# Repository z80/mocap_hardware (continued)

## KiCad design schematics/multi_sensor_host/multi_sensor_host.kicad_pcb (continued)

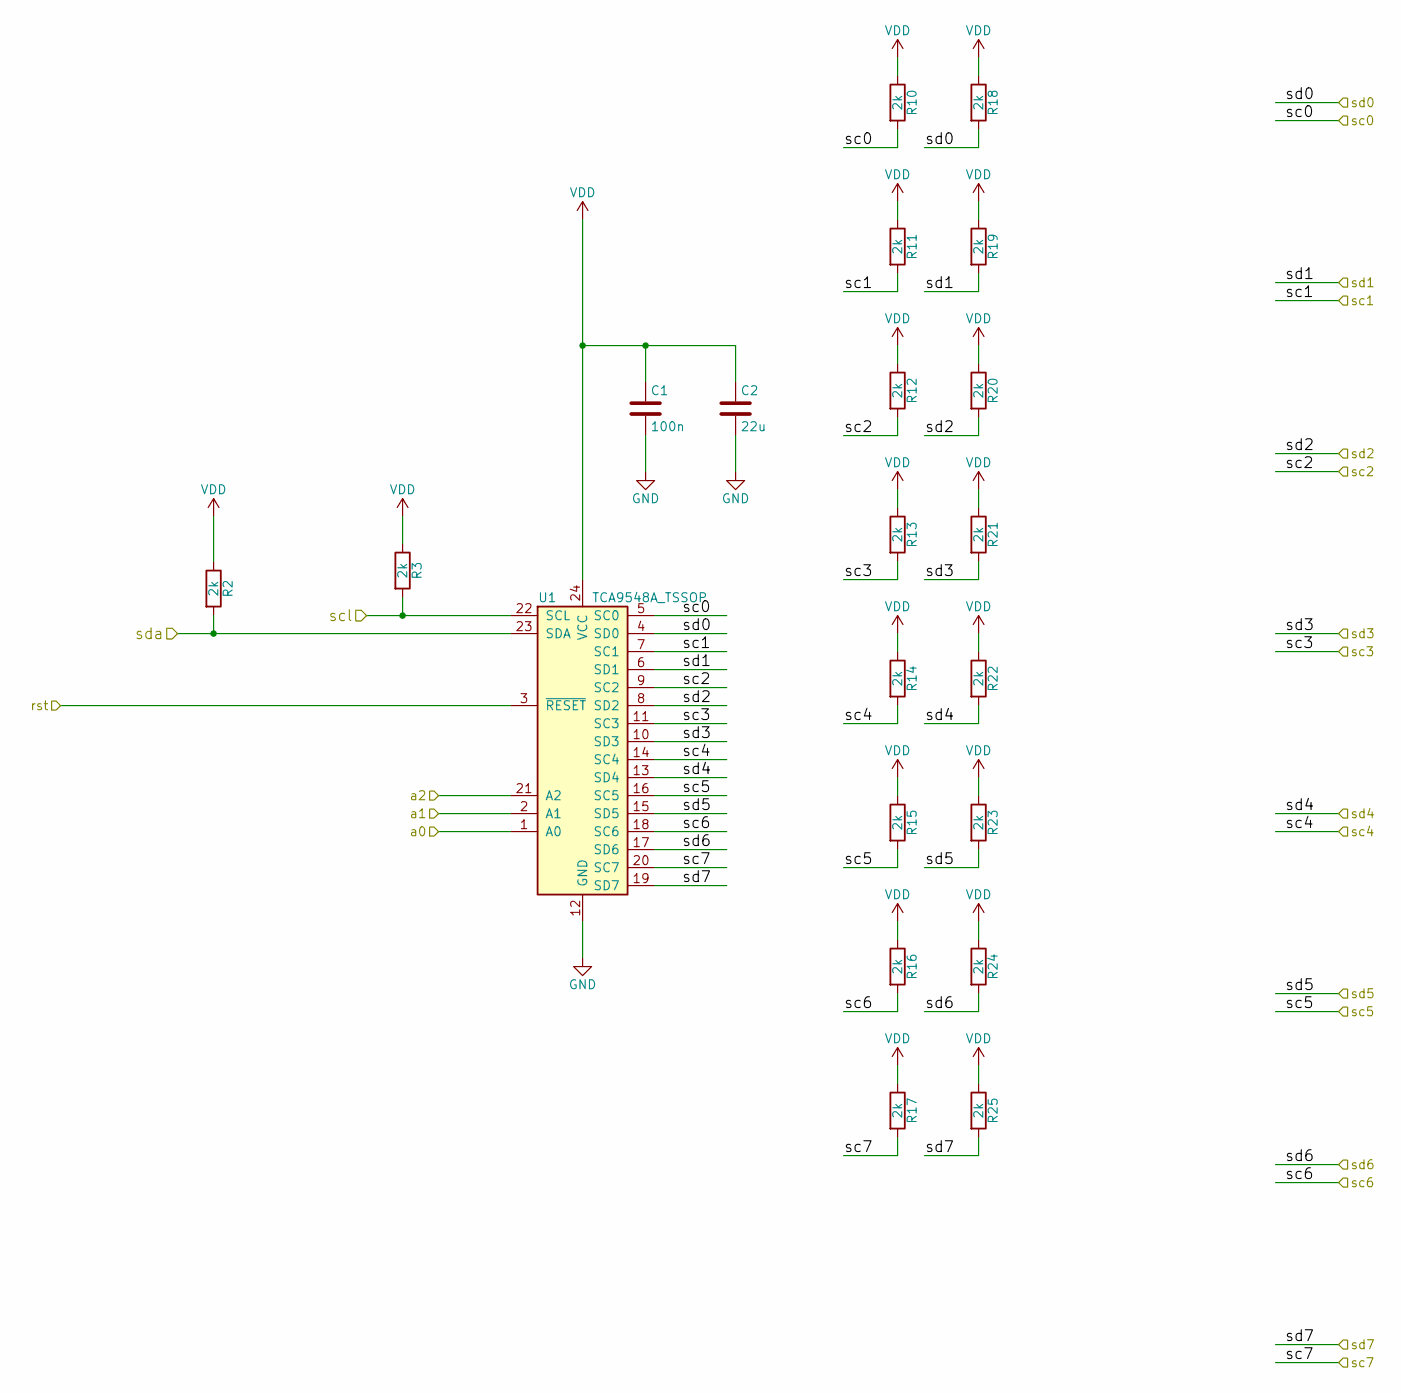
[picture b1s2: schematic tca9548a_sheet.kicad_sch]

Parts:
C1: 100n; C_0603_1608Metric
C2: 22u; C_0603_1608Metric
R2, R3, R10, R11, R12, R13, R14, R15, R16, R17, R18, R19, R20, R21, R22, R23, R24, R25: 2k; C_0603_1608Metric
U1: TCA9548A_TSSOP; TSSOP-24_4.4x7.8mm_P0.65mm

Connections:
/rst_mcu: U1.3 (~RESET); also elsewhere on the board
/scl_0: R10.2, U1.5 (SC0); also elsewhere on the board
/scl_1: R11.2, U1.7 (SC1); also elsewhere on the board
/scl_2: R12.2, U1.9 (SC2); also elsewhere on the board
/scl_3: R13.2, U1.11 (SC3); also elsewhere on the board
/scl_4: R14.2, U1.14 (SC4); also elsewhere on the board
/scl_5: R15.2, U1.16 (SC5); also elsewhere on the board
/scl_6: R16.2, U1.18 (SC6); also elsewhere on the board
/scl_7: R17.2, U1.20 (SC7); also elsewhere on the board
/scl_host_a: R3.2, U1.22 (SCL); also elsewhere on the board
/sda_0: R18.2, U1.4 (SD0); also elsewhere on the board
/sda_1: R19.2, U1.6 (SD1); also elsewhere on the board
/sda_2: R20.2, U1.8 (SD2); also elsewhere on the board
/sda_3: R21.2, U1.10 (SD3); also elsewhere on the board
/sda_4: R22.2, U1.13 (SD4); also elsewhere on the board
/sda_5: R23.2, U1.15 (SD5); also elsewhere on the board
/sda_6: R24.2, U1.17 (SD6); also elsewhere on the board
/sda_7: R25.2, U1.19 (SD7); also elsewhere on the board
/sda_host_a: R2.2, U1.23 (SDA); also elsewhere on the board
GND: C1.2, C2.2, U1.1 (A0), U1.2 (A1), U1.12 (GND), U1.21 (A2); also elsewhere on the board
VDD: C1.1, C2.1, R2.1, R3.1, R10.1, R11.1, R12.1, R13.1, R14.1, R15.1, R16.1, R17.1, R18.1, R19.1, R20.1, R21.1, R22.1, R23.1, R24.1, R25.1, U1.24 (VCC); also elsewhere on the board

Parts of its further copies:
C11, C13: 100n; C_0603_1608Metric
C12, C14: 22u; C_0603_1608Metric
R4, R5, R6, R7, R8, R9, R26, R27, R28, R29, R30, R31, R32, R33, R34, R35, R36, R37, R38, R39, R40, R41, R42, R43, R44, R45, R46, R47, R48, R49, R50, R51, R52, R53, R54, R55: 2k; C_0603_1608Metric
U2, U3: TCA9548A_TSSOP; TSSOP-24_4.4x7.8mm_P0.65mm

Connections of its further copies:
/rst_mcu: U2.3 (~RESET), U3.3 (~RESET); also elsewhere on the board
/scl_8: R7.2, U2.5 (SC0); also elsewhere on the board
/scl_9: R8.2, U2.7 (SC1); also elsewhere on the board
/scl_10: R9.2, U2.9 (SC2); also elsewhere on the board
/scl_11: R26.2, U2.11 (SC3); also elsewhere on the board
/scl_12: R27.2, U2.14 (SC4); also elsewhere on the board
/scl_13: R28.2, U2.16 (SC5); also elsewhere on the board
/scl_14: R29.2, U2.18 (SC6); also elsewhere on the board
/scl_15: R30.2, U2.20 (SC7); also elsewhere on the board
/scl_16: R40.2, U3.5 (SC0); also elsewhere on the board
/scl_17: R41.2, U3.7 (SC1); also elsewhere on the board
/scl_18: R42.2, U3.9 (SC2); also elsewhere on the board
/scl_19: R43.2, U3.11 (SC3); also elsewhere on the board
/scl_20: R44.2, U3.14 (SC4); also elsewhere on the board
/scl_21: R45.2, U3.16 (SC5); also elsewhere on the board
/scl_22: R46.2, U3.18 (SC6); also elsewhere on the board
/scl_23: R47.2, U3.20 (SC7); also elsewhere on the board
/scl_host_b: R6.2, U2.22 (SCL); also elsewhere on the board
/scl_host_c: R39.2, U3.22 (SCL); also elsewhere on the board
/sda_8: R31.2, U2.4 (SD0); also elsewhere on the board
/sda_9: R32.2, U2.6 (SD1); also elsewhere on the board
/sda_10: R33.2, U2.8 (SD2); also elsewhere on the board
/sda_11: R34.2, U2.10 (SD3); also elsewhere on the board
/sda_12: R35.2, U2.13 (SD4); also elsewhere on the board
/sda_13: R36.2, U2.15 (SD5); also elsewhere on the board
/sda_14: R37.2, U2.17 (SD6); also elsewhere on the board
/sda_15: R38.2, U2.19 (SD7); also elsewhere on the board
/sda_16: R48.2, U3.4 (SD0); also elsewhere on the board
/sda_17: R49.2, U3.6 (SD1); also elsewhere on the board
/sda_18: R50.2, U3.8 (SD2); also elsewhere on the board
/sda_19: R51.2, U3.10 (SD3); also elsewhere on the board
/sda_20: R52.2, U3.13 (SD4); also elsewhere on the board
/sda_21: R53.2, U3.15 (SD5); also elsewhere on the board
/sda_22: R54.2, U3.17 (SD6); also elsewhere on the board
/sda_23: R55.2, U3.19 (SD7); also elsewhere on the board
/sda_host_b: R5.2, U2.23 (SDA); also elsewhere on the board
/sda_host_c: R4.2, U3.23 (SDA); also elsewhere on the board
GND: C11.2, C12.2, C13.2, C14.2, U2.1 (A0), U2.2 (A1), U2.12 (GND), U2.21 (A2), U3.1 (A0), U3.2 (A1), U3.12 (GND), U3.21 (A2); also elsewhere on the board
VDD: C11.1, C12.1, C13.1, C14.1, R4.1, R5.1, R6.1, R7.1, R8.1, R9.1, R26.1, R27.1, R28.1, R29.1, R30.1, R31.1, R32.1, R33.1, R34.1, R35.1, R36.1, R37.1, R38.1, R39.1, R40.1, R41.1, R42.1, R43.1, R44.1, R45.1, R46.1, R47.1, R48.1, R49.1, R50.1, R51.1, R52.1, R53.1, R54.1, R55.1, U2.24 (VCC), U3.24 (VCC); also elsewhere on the board

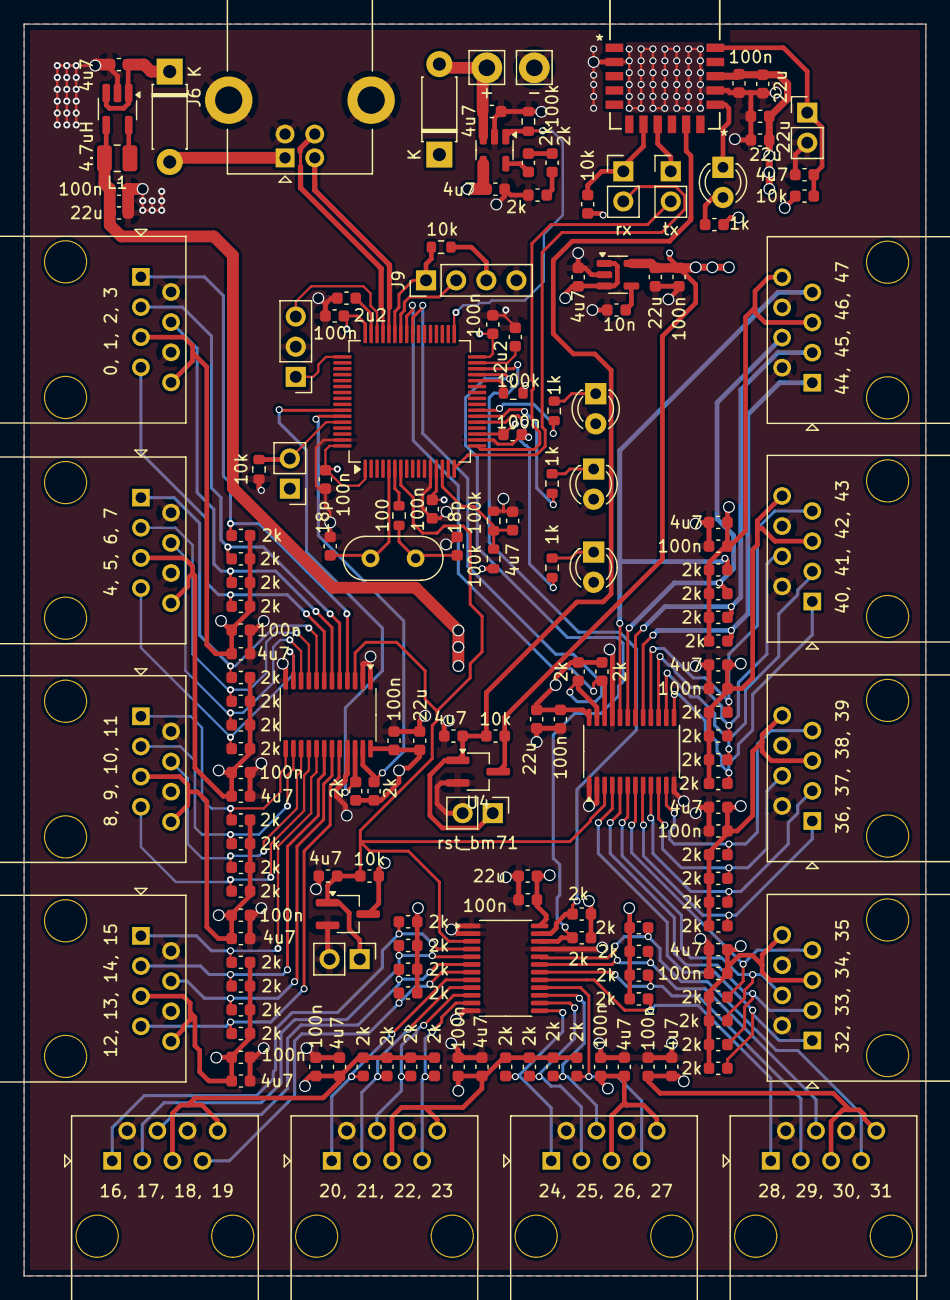
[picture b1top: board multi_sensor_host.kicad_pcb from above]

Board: 4 copper layers, 76.0 x 105.5 mm, 169 parts (0 on the bottom side), 95 nets.

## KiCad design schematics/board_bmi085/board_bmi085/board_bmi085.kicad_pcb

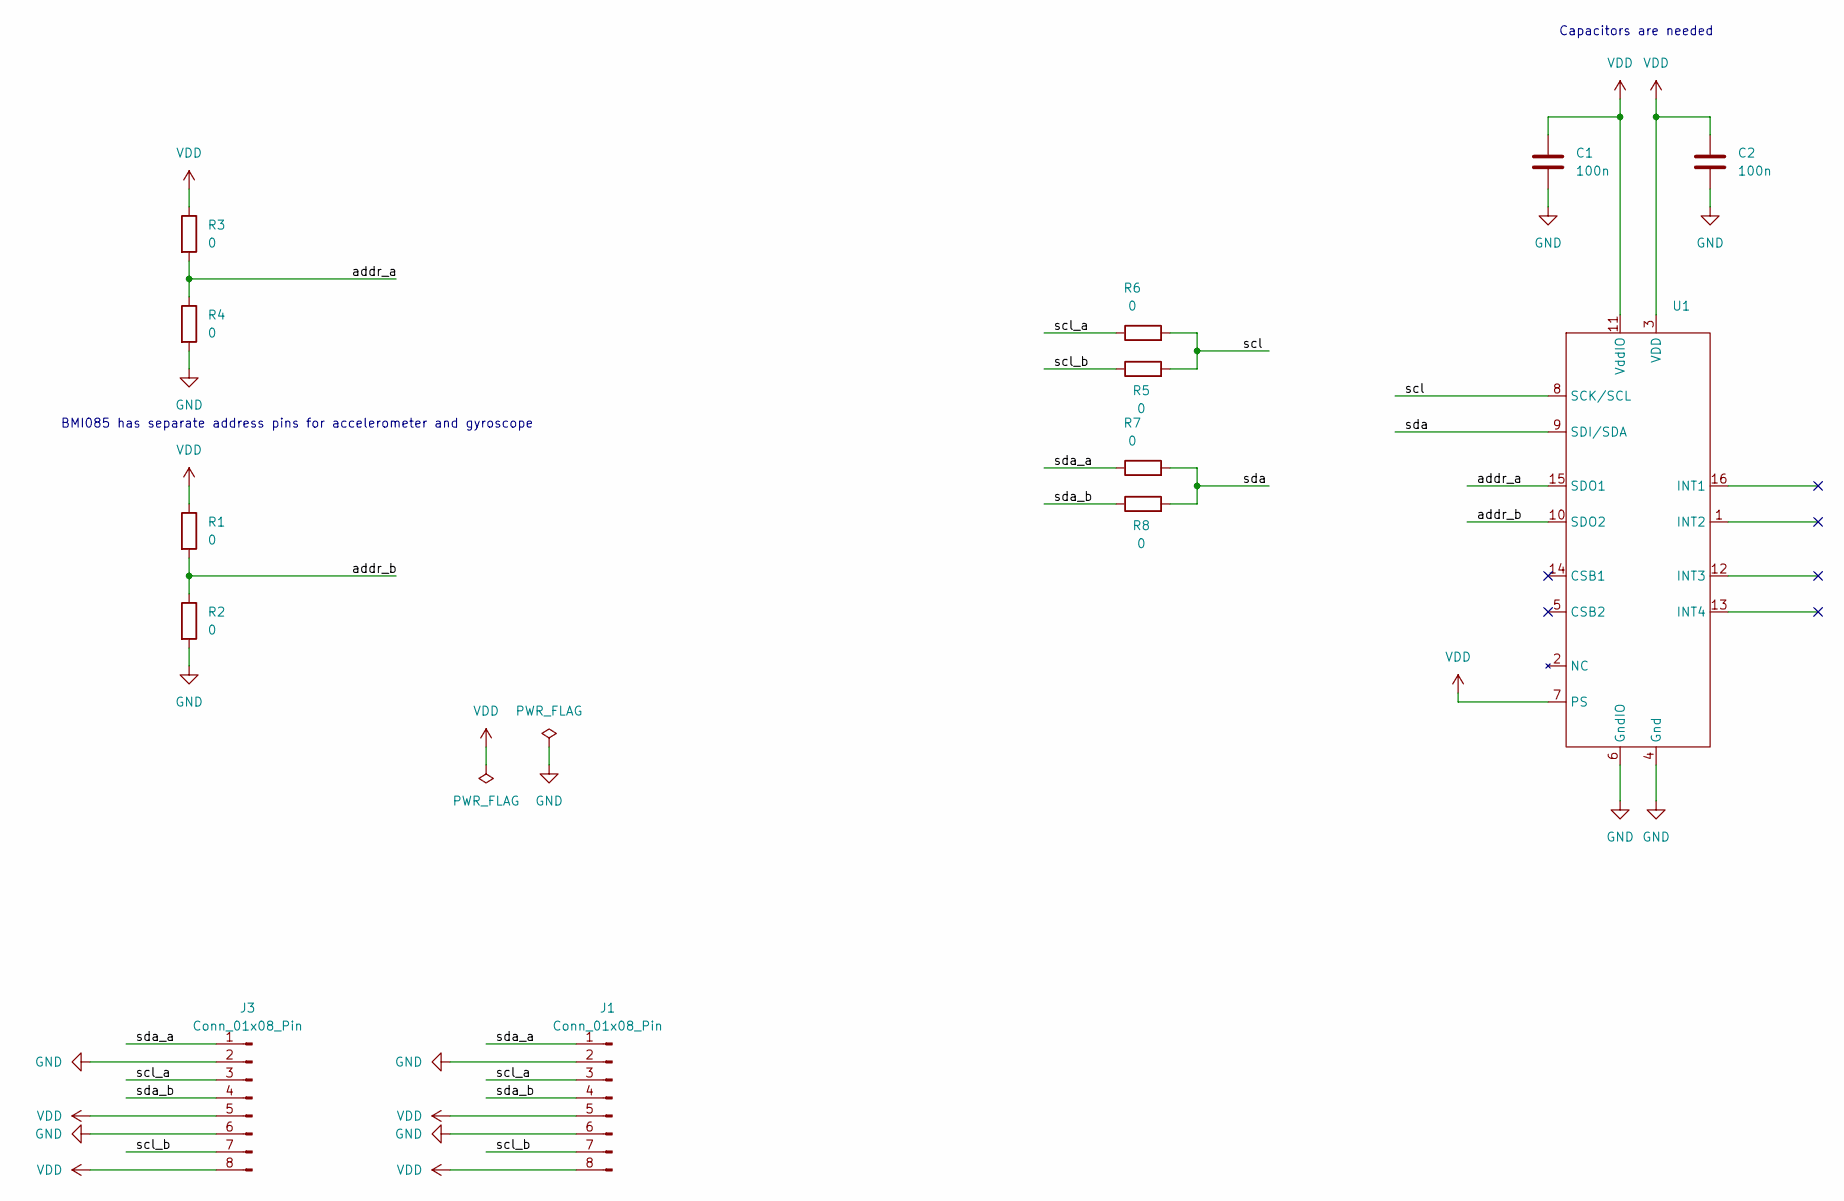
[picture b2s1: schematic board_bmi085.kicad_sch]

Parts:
C1, C2: 100n; C_0603_1608Metric
J1, J3: Conn_01x08_Pin; PinHeader_1x08_P1.27mm_Vertical
R1, R2, R3, R4, R5, R6, R7, R8: 0; R_0402_1005Metric
U1: BMI085

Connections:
/addr_a: R3.2, R4.1, U1.15 (SDO1)
/addr_b: R1.2, R2.1, U1.10 (SDO2)
/scl: R5.2, R6.2, U1.8 (SCK/SCL)
/scl_a: J1.3, J3.3, R6.1
/scl_b: J1.7, J3.7, R5.1
/sda: R7.2, R8.2, U1.9 (SDI/SDA)
/sda_a: J1.1, J3.1, R7.1
/sda_b: J1.4, J3.4, R8.1
GND: C1.2, C2.2, J1.2, J1.6, J3.2, J3.6, R2.2, R4.2, U1.4 (Gnd), U1.6 (GndIO)
VDD: C1.1, C2.1, J1.5, J1.8, J3.5, J3.8, R1.1, R3.1, U1.3 (VDD), U1.7 (PS), U1.11 (VddIO)

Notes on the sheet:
Capacitors are needed
BMI085 has separate address pins for accelerometer and gyroscope

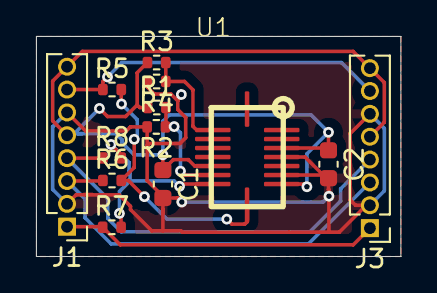
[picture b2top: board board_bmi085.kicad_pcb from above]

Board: 2 copper layers, 20.2 x 12.2 mm, 13 parts (0 on the bottom side), 10 nets.

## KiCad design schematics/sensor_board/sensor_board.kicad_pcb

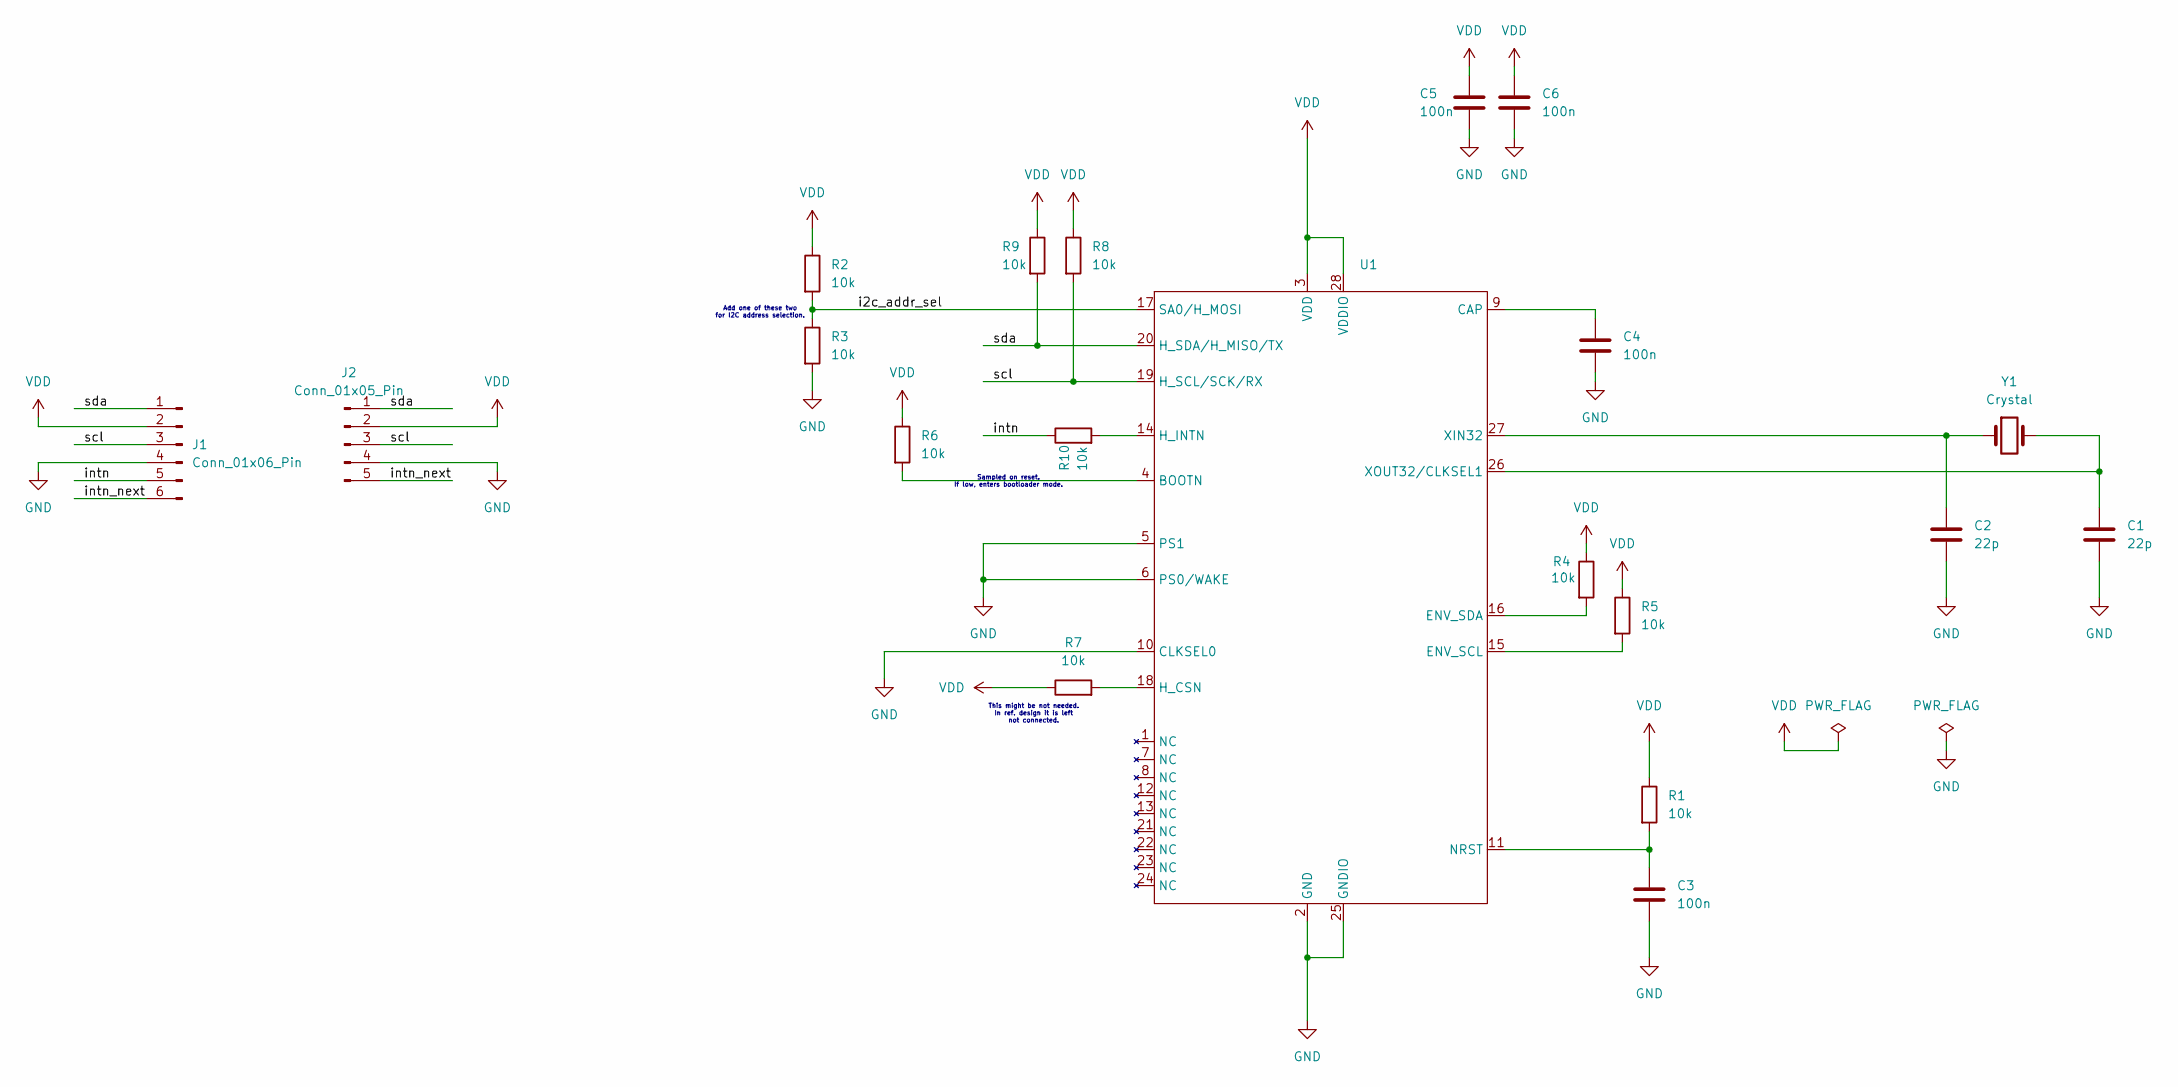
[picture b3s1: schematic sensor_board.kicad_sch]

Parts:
C1, C2: 22p; C_0603_1608Metric_Pad1.08x0.95mm_HandSolder
C3, C4, C5, C6: 100n; C_0603_1608Metric_Pad1.08x0.95mm_HandSolder
J1: Conn_01x06_Pin; PinHeader_1x06_P1.27mm_Vertical
J2: Conn_01x05_Pin; PinHeader_1x05_P1.27mm_Vertical
R1, R2, R3, R4, R5, R6, R7, R8, R9, R10: 10k; R_0603_1608Metric_Pad0.98x0.95mm_HandSolder
U1: LGA-28_5.2x3.8mm_P0.5mm
Y1: Crystal; Crystal_HC52-8mm_Vertical

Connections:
/i2c_addr_sel: R2.2, R3.1, U1.17 (SA0/H_MOSI)
/intn: J1.5, R10.1
/intn_next: J1.6, J2.5
/scl: J1.3, J2.3, R8.2, U1.19 (H_SCL/SCK/RX)
/sda: J1.1, J2.1, R9.2, U1.20 (H_SDA/H_MISO/TX)
GND: C1.2, C2.2, C3.2, C4.2, C5.2, C6.2, J1.4, J2.4, R3.2, U1.2 (GND), U1.5 (PS1), U1.6 (PS0/WAKE), U1.10 (CLKSEL0), U1.25 (GNDIO)
unnamed: R6.2, U1.4 (BOOTN)
unnamed: C4.1, U1.9 (CAP)
unnamed: R5.2, U1.15 (ENV_SCL)
unnamed: R4.2, U1.16 (ENV_SDA)
unnamed: R7.2, U1.18 (H_CSN)
unnamed: R10.2, U1.14 (H_INTN)
unnamed: C3.1, R1.2, U1.11 (NRST)
unnamed: C2.1, U1.27 (XIN32), Y1.1
unnamed: C1.1, U1.26 (XOUT32/CLKSEL1), Y1.2
VDD: C5.1, C6.1, J1.2, J2.2, R1.1, R2.1, R4.1, R5.1, R6.1, R7.1, R8.1, R9.1, U1.3 (VDD), U1.28 (VDDIO)

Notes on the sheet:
Sampled on reset. If low, enters bootloader mode.
Add one of these two for I2C address selection.
This might be not needed. In ref. design it is left not connected.

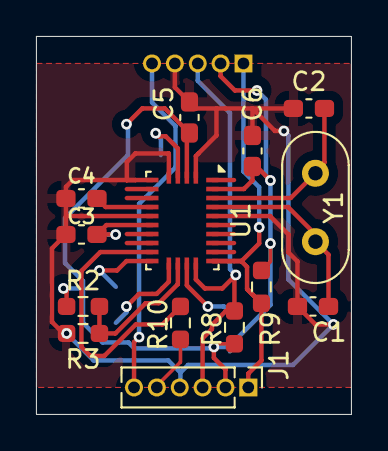
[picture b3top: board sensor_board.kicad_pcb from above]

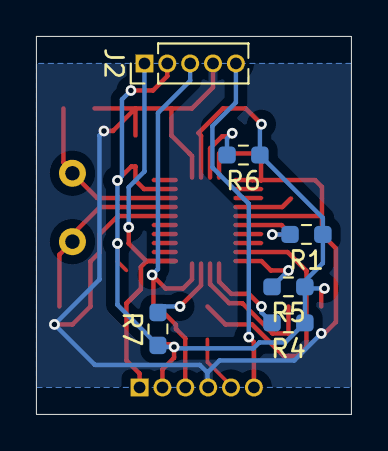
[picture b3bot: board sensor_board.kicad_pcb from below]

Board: 2 copper layers, 17.5 x 21.0 mm, 20 parts (6 on the bottom side), 16 nets.

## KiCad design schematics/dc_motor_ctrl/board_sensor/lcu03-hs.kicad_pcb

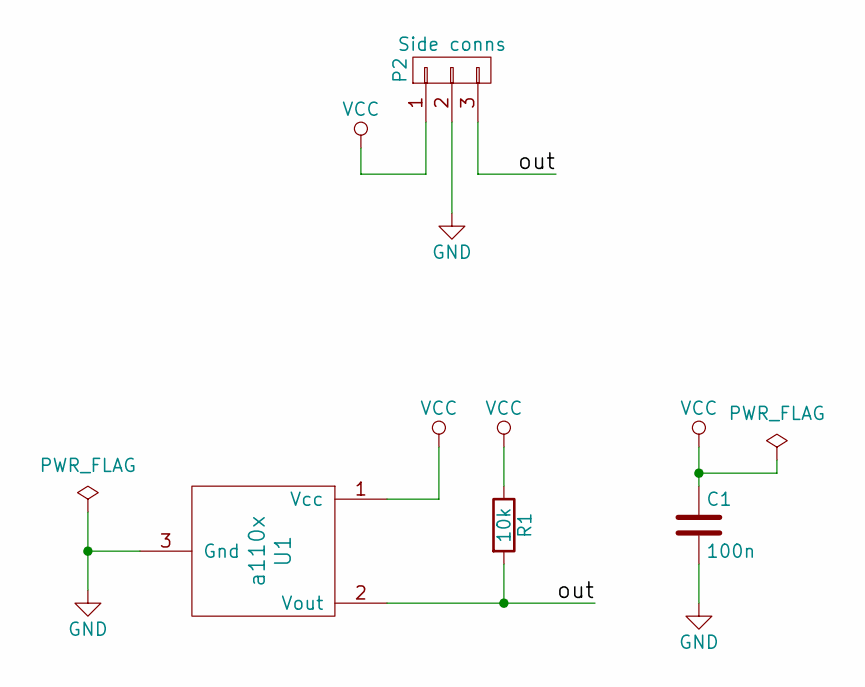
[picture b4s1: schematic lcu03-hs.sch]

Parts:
C1: 100n; C_0603
P2: Side conns; Pin_Header_Angled_1x03
R1: 10k; R_0603
U1: a110x; SOT-23-wide

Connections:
/out: P2.3, R1.2, U1.2 (Vout)
GND: C1.2, P2.2, U1.3 (Gnd)
VCC: C1.1, P2.1, R1.1, U1.1 (Vcc)

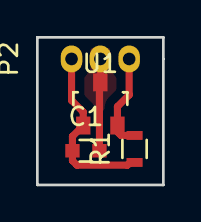
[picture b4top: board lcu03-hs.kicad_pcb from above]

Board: 2 copper layers, 7.0 x 8.2 mm, 4 parts (0 on the bottom side), 3 nets.

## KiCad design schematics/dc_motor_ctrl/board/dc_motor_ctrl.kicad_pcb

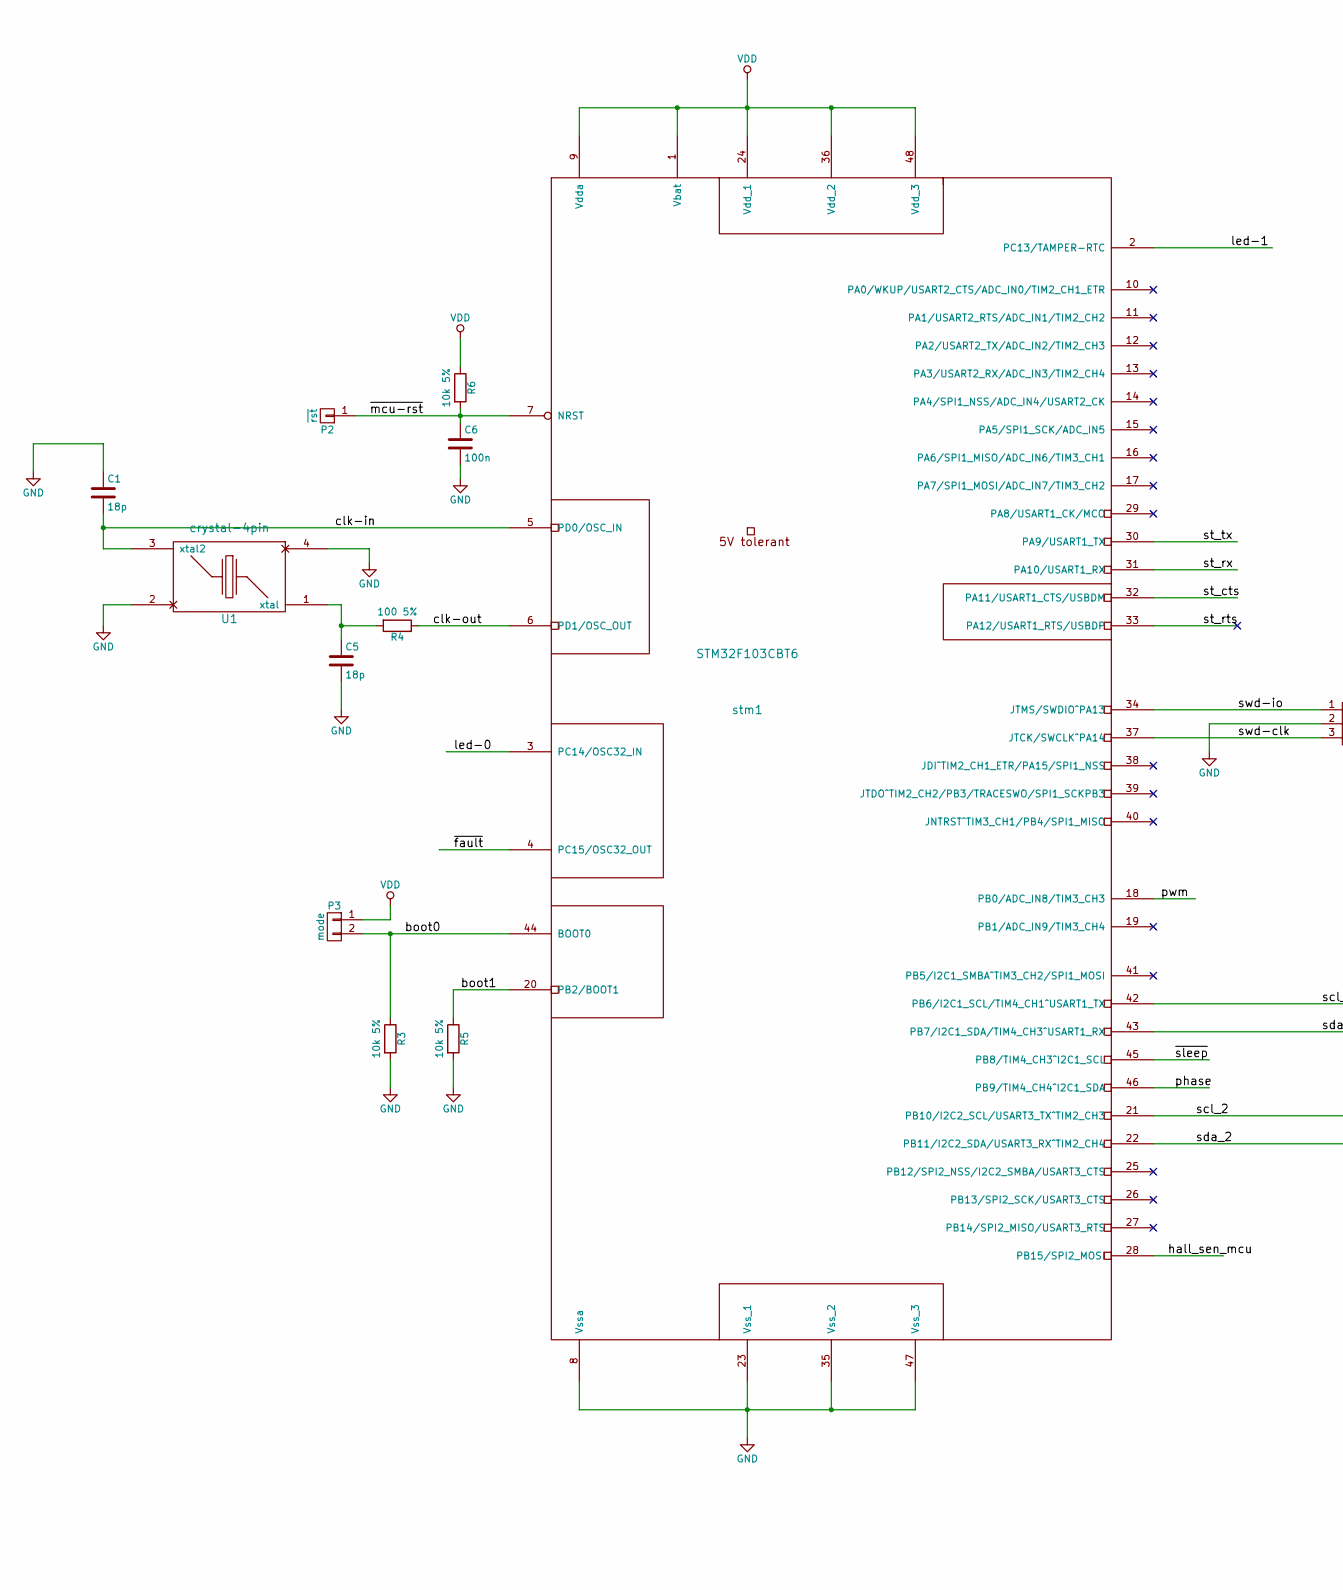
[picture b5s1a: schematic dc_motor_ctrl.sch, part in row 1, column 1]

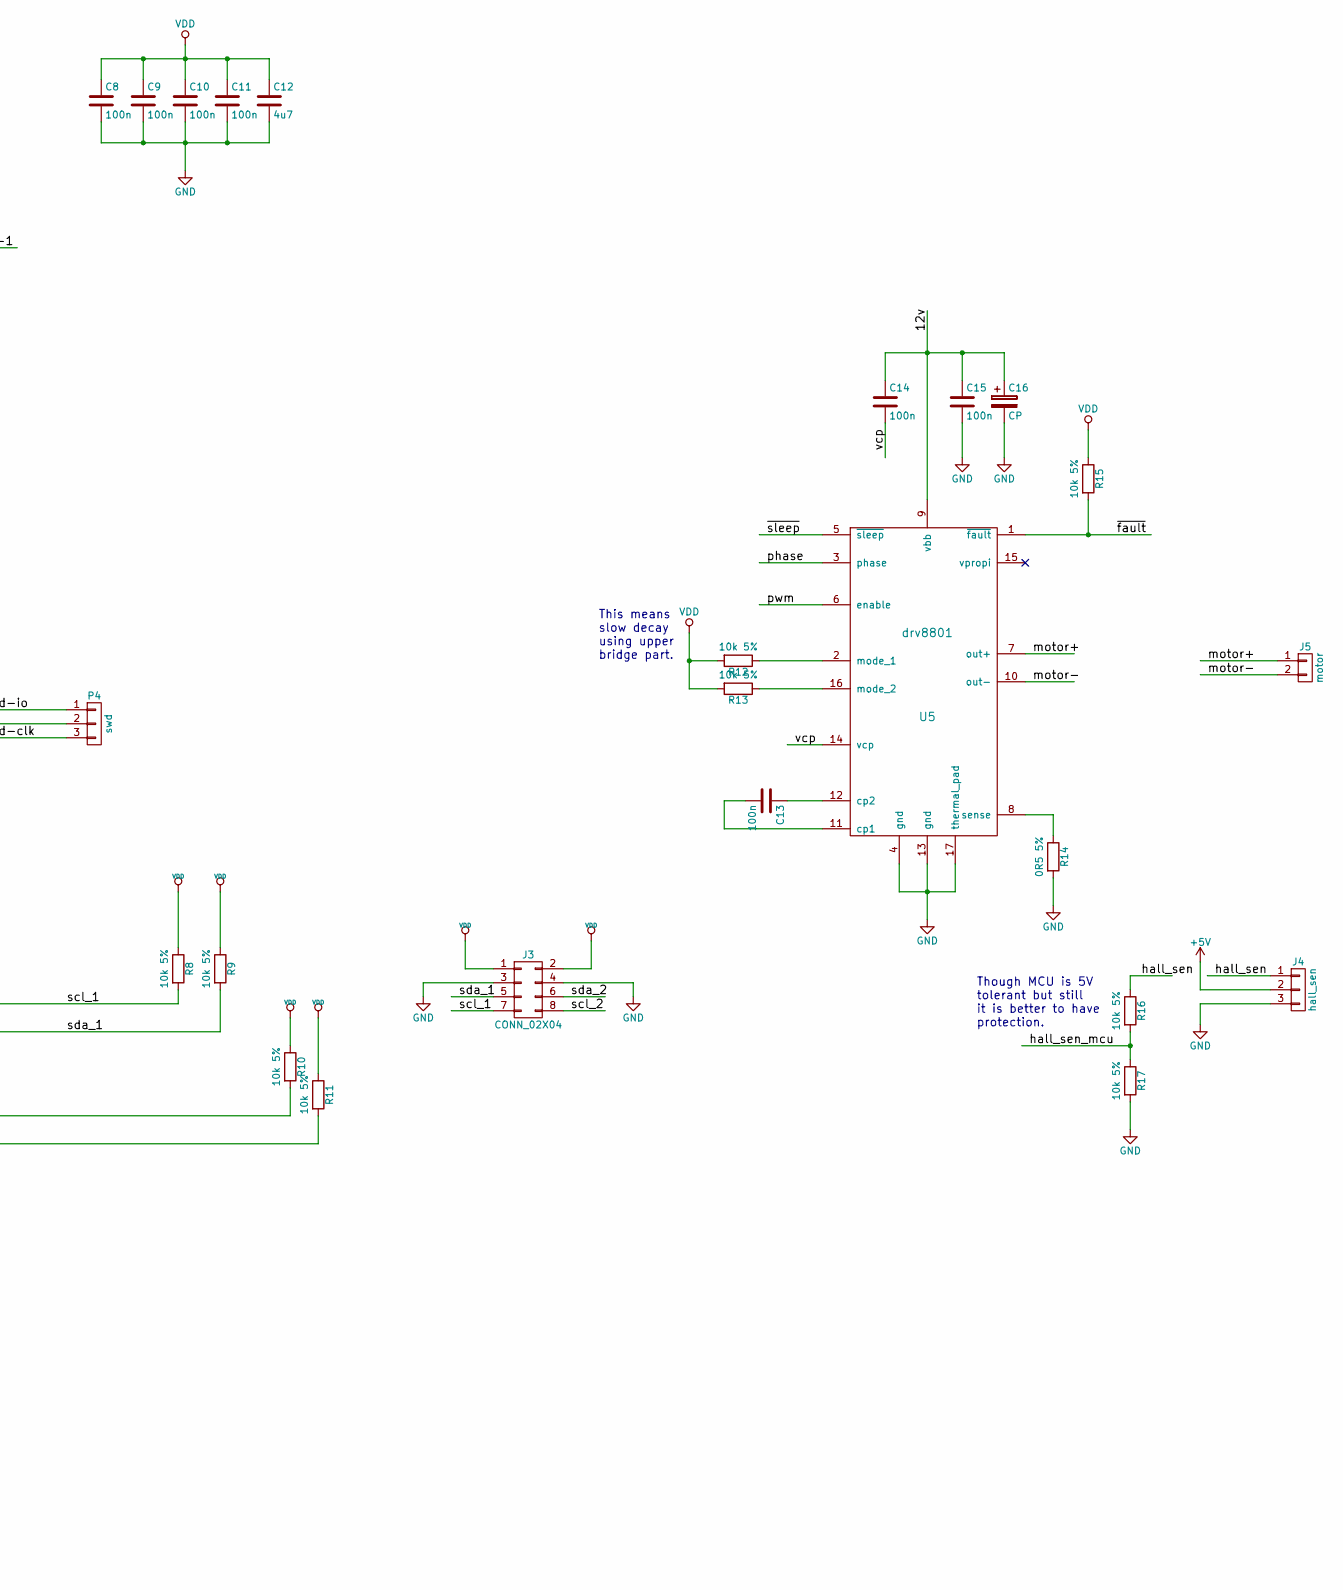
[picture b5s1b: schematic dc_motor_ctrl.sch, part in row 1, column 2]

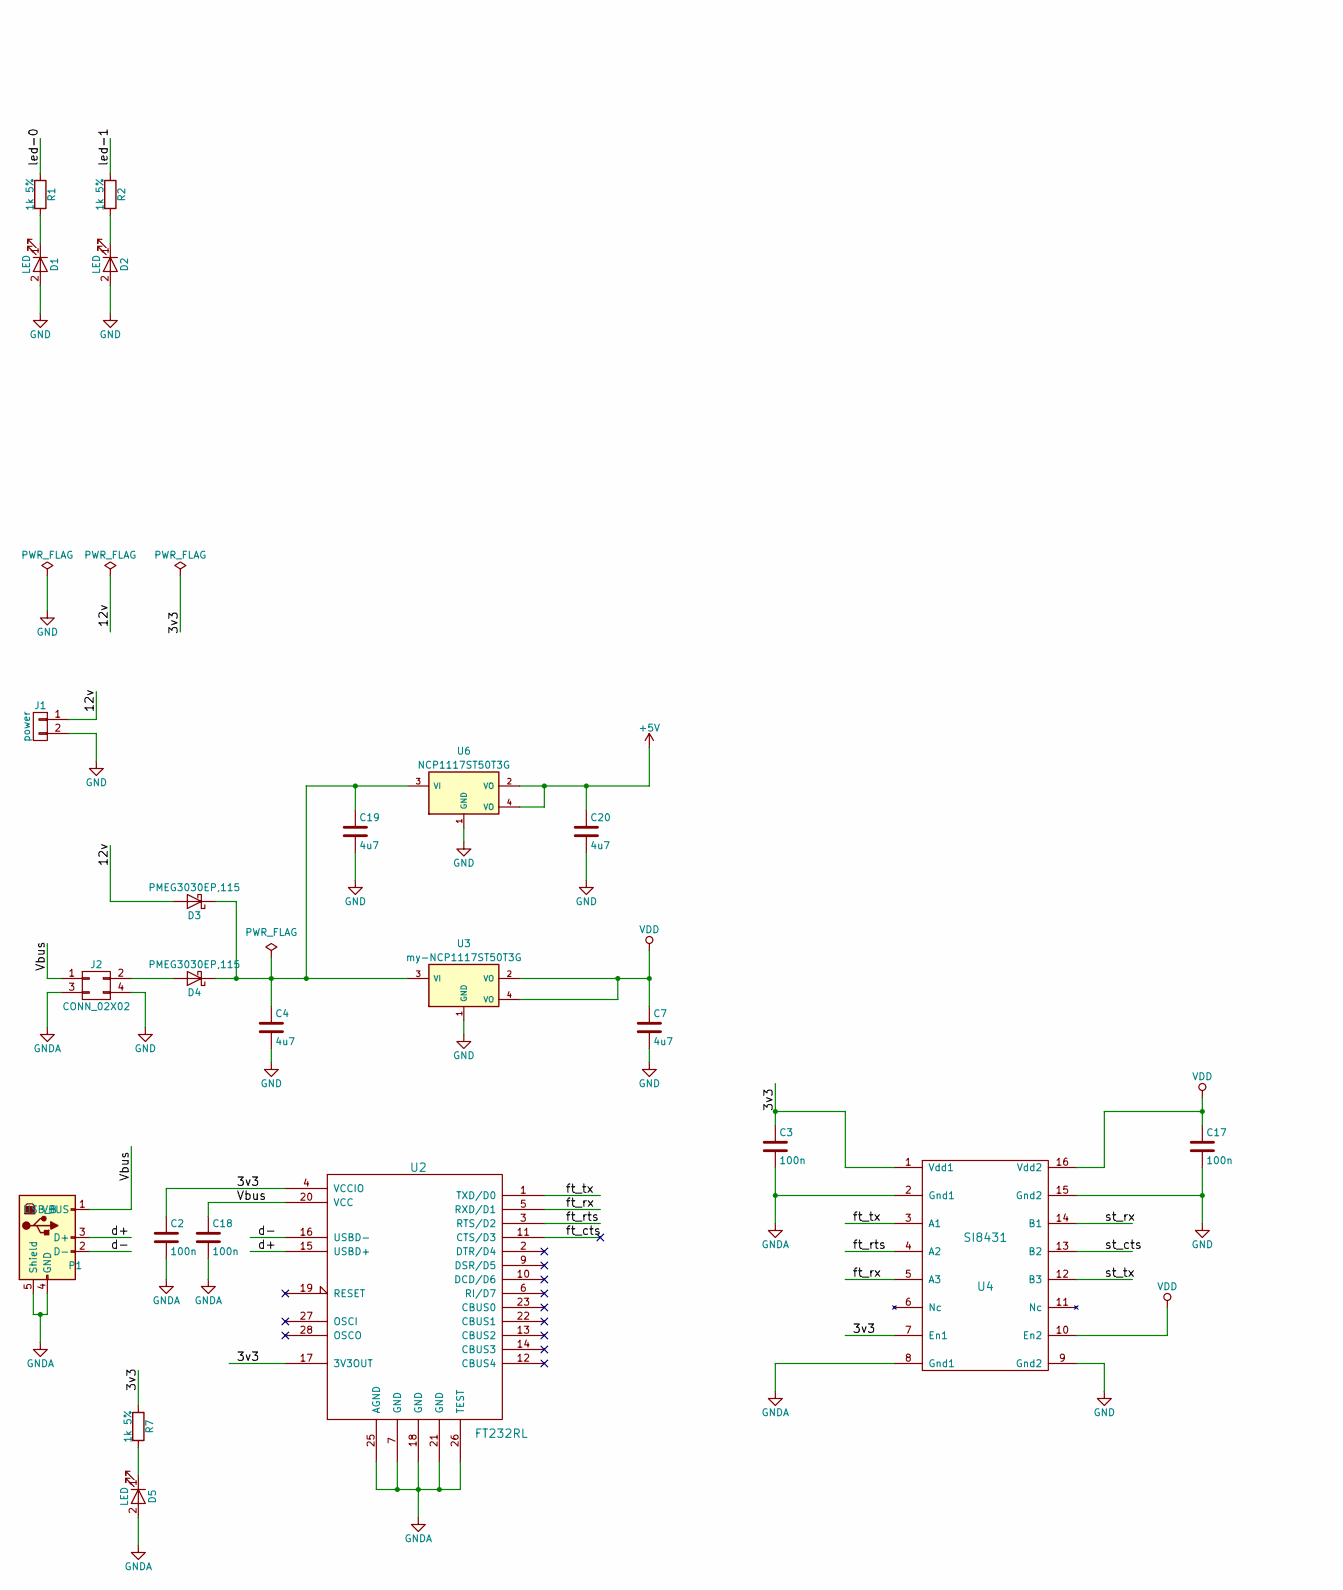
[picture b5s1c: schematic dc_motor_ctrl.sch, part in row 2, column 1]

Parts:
C1, C5: 18p; C_0603_HandSoldering
C2, C3, C6, C8, C9, C10, C11, C13, C14, C15, C17, C18: 100n; C_0603_HandSoldering
C4, C7, C12, C19, C20: 4u7; C_0603_HandSoldering
C16: CP; CP_Radial_D10.0mm_P5.00mm
D1, D2, D5: LED; LED_D5.0mm
D3, D4: PMEG3030EP,115; SOD128
J1: power; Pin_Header_Straight_1x02_Pitch2.54mm
J2: CONN_02X02; Pin_Header_Straight_2x02_Pitch2.54mm
J3: CONN_02X04; Pin_Header_Straight_2x04_Pitch2.54mm
J4: hall_sen; Pin_Header_Straight_1x03_Pitch1.27mm
J5: motor; Pin_Header_Straight_1x02_Pitch2.54mm
P1: USB_B
P2: ~rst~; Pin_Header_Straight_1x01_Pitch1.27mm
P3: mode; Pin_Header_Straight_1x02_Pitch1.27mm
P4: swd; Pin_Header_Straight_1x03_Pitch1.27mm
R1, R2, R7: 1k 5%; R_0603_HandSoldering
R3, R5, R6, R8, R9, R10, R11, R12, R13, R15, R16, R17: 10k 5%; R_0603_HandSoldering
R4: 100 5%; R_0603_HandSoldering
R14: 0R5 5%; R_0603_HandSoldering
U1: crystal-4pin; CRYSTAL-SMD-5x3
U2: FT232RL; SSOP-28_5.3x10.2mm_Pitch0.65mm
U3: my-NCP1117ST50T3G; SOT-223
U4: SI8431; SOIC-16W_7.5x10.3mm_Pitch1.27mm
U5: drv8801; my_TSSOP-16-1EP_4.4x5mm_Pitch0.65mm
U6: NCP1117ST50T3G; SOT-223
stm1: STM32F103CBT6; LQFP48

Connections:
+5V: C20.1, J4.2, U6.2 (VO), U6.4 (VO)
/3v3: C2.1, C3.1, R7.1, U2.4 (VCCIO), U2.17 (3V3OUT), U4.1 (Vdd1), U4.7 (En1)
/12v: C14.1, C15.1, C16.1, D3.2 (A), J1.1, U5.9 (vbb)
/Vbus: C18.1, J2.1, P1.1 (VBUS), U2.20 (VCC)
/boot0: P3.2, R3.1, stm1.44 (BOOT0)
/boot1: R5.1, stm1.20 (PB2/BOOT1)
/clk-in: C1.2, U1.3 (xtal2), stm1.5 (PD0/OSC_IN)
/clk-out: R4.1, stm1.6 (PD1/OSC_OUT)
/d+: P1.3 (D+), U2.15 (USBD+)
/d-: P1.2 (D-), U2.16 (USBD-)
/ft_rts: U2.3 (RTS/D2), U4.4 (A2)
/ft_rx: U2.5 (RXD/D1), U4.5 (A3)
/ft_tx: U2.1 (TXD/D0), U4.3 (A1)
/hall_sen: J4.1, R16.1
/hall_sen_mcu: R16.2, R17.1, stm1.28 (PB15/SPI2_MOSI)
/led-0: R1.1, stm1.3 (PC14/OSC32_IN)
/led-1: R2.1, stm1.2 (PC13/TAMPER-RTC)
/motor+: J5.1, U5.7 (out+)
/motor-: J5.2, U5.10 (out-)
/phase: U5.3 (phase), stm1.46 (PB9/TIM4_CH4^I2C1_SDA)
/pwm: U5.6 (enable), stm1.18 (PB0/ADC_IN8/TIM3_CH3)
/scl_1: J3.7, R8.2, stm1.42 (PB6/I2C1_SCL/TIM4_CH1^USART1_TX)
/scl_2: J3.8, R10.2, stm1.21 (PB10/I2C2_SCL/USART3_TX^TIM2_CH3)
/sda_1: J3.5, R9.2, stm1.43 (PB7/I2C1_SDA/TIM4_CH3^USART1_RX)
/sda_2: J3.6, R11.2, stm1.22 (PB11/I2C2_SDA/USART3_RX^TIM2_CH4)
/st_cts: U4.13 (B2), stm1.32 (PA11/USART1_CTS/USBDM)
/st_rx: U4.14 (B1), stm1.31 (PA10/USART1_RX)
/st_tx: U4.12 (B3), stm1.30 (PA9/USART1_TX)
/swd-clk: P4.3, stm1.37 (JTCK/SWCLK^PA14)
/swd-io: P4.1, stm1.34 (JTMS/SWDIO^PA13)
/vcp: C14.2, U5.14 (vcp)
/~fault~: R15.2, U5.1 (~fault~), stm1.4 (PC15/OSC32_OUT)
/~mcu-rst~: C6.1, P2.1, R6.2, stm1.7 (NRST)
/~sleep~: U5.5 (~sleep~), stm1.45 (PB8/TIM4_CH3^I2C1_SCL)
GND: C1.1, C4.2, C5.2, C6.2, C7.2, C8.2, C9.2, C10.2, C11.2, C12.2, C15.2, C16.2, C17.2, C19.2, C20.2, D1.2 (A), D2.2 (A), J1.2, J2.4, J3.3, J3.4, J4.3, P4.2, R3.2, R5.2, R14.2, R17.2, U1.2, U1.4, U3.1 (GND), U4.9 (Gnd2), U4.15 (Gnd2), U5.4 (gnd), U5.13 (gnd), U5.17 (thermal_pad), U6.1 (GND), stm1.8 (Vssa), stm1.23 (Vss_1), stm1.35 (Vss_2), stm1.47 (Vss_3)
GNDA: C2.2, C3.2, C18.2, D5.2 (A), J2.3, P1.4 (GND), P1.5 (Shield), U2.7 (GND), U2.18 (GND), U2.21 (GND), U2.25 (AGND), U2.26 (TEST), U4.2 (Gnd1), U4.8 (Gnd1)
unnamed: C5.1, R4.2, U1.1 (xtal)
unnamed: C13.1, U5.12 (cp2)
unnamed: C13.2, U5.11 (cp1)
unnamed: C4.1, C19.1, D3.1 (K), D4.1 (K), U3.3 (VI), U6.3 (VI)
unnamed: D1.1 (K), R1.2
unnamed: D2.1 (K), R2.2
unnamed: D4.2 (A), J2.2
unnamed: D5.1 (K), R7.2
unnamed: R12.1, U5.2 (mode_1)
unnamed: R13.1, U5.16 (mode_2)
unnamed: R14.1, U5.8 (sense)
VDD: C7.1, C8.1, C9.1, C10.1, C11.1, C12.1, C17.1, J3.1, J3.2, P3.1, R6.1, R8.1, R9.1, R10.1, R11.1, R12.2, R13.2, R15.1, U3.2 (VO), U3.4 (VO), U4.10 (En2), U4.16 (Vdd2), stm1.1 (Vbat), stm1.9 (Vdda), stm1.24 (Vdd_1), stm1.36 (Vdd_2), stm1.48 (Vdd_3)

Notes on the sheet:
This means slow decay using upper bridge part.
Though MCU is 5V tolerant but still it is better to have protection.

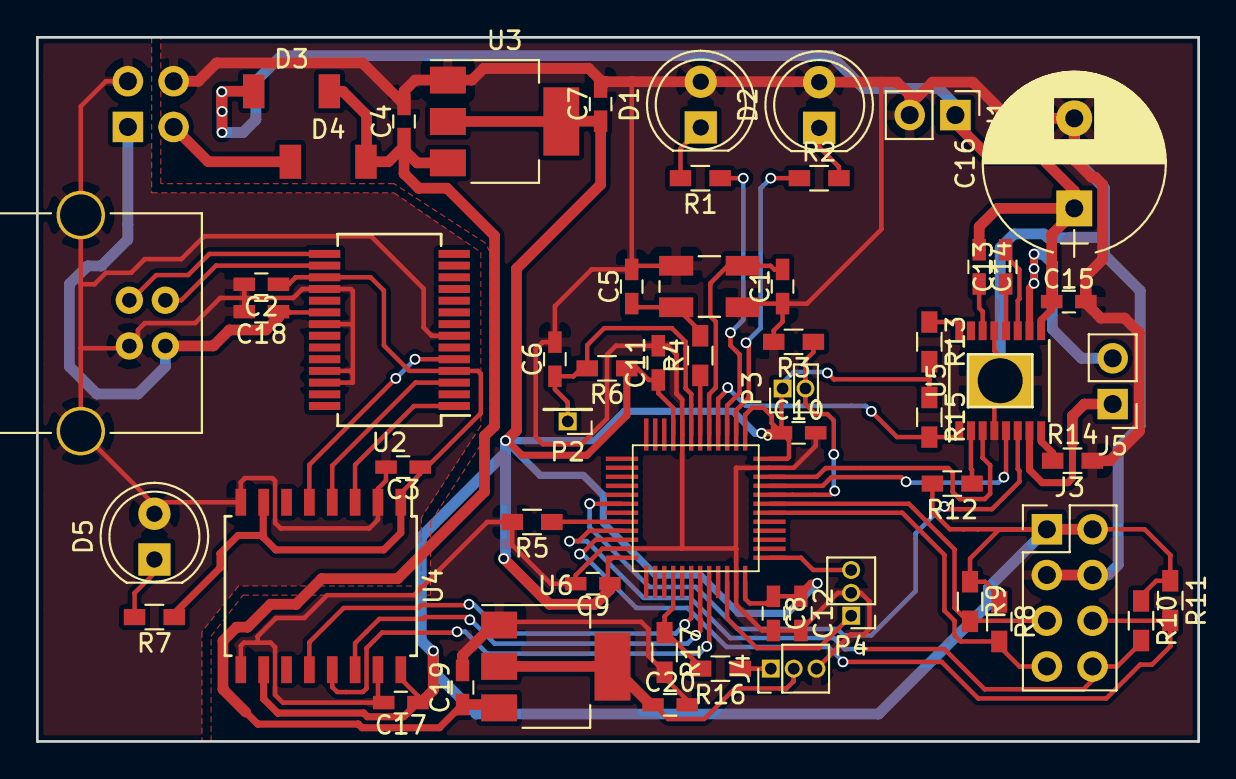
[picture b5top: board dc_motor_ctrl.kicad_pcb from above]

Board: 2 copper layers, 64.5 x 39.1 mm, 58 parts (1 on the bottom side), 48 nets.
